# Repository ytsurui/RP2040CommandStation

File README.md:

# RP2040-Based DCC Command Station

underconstruction

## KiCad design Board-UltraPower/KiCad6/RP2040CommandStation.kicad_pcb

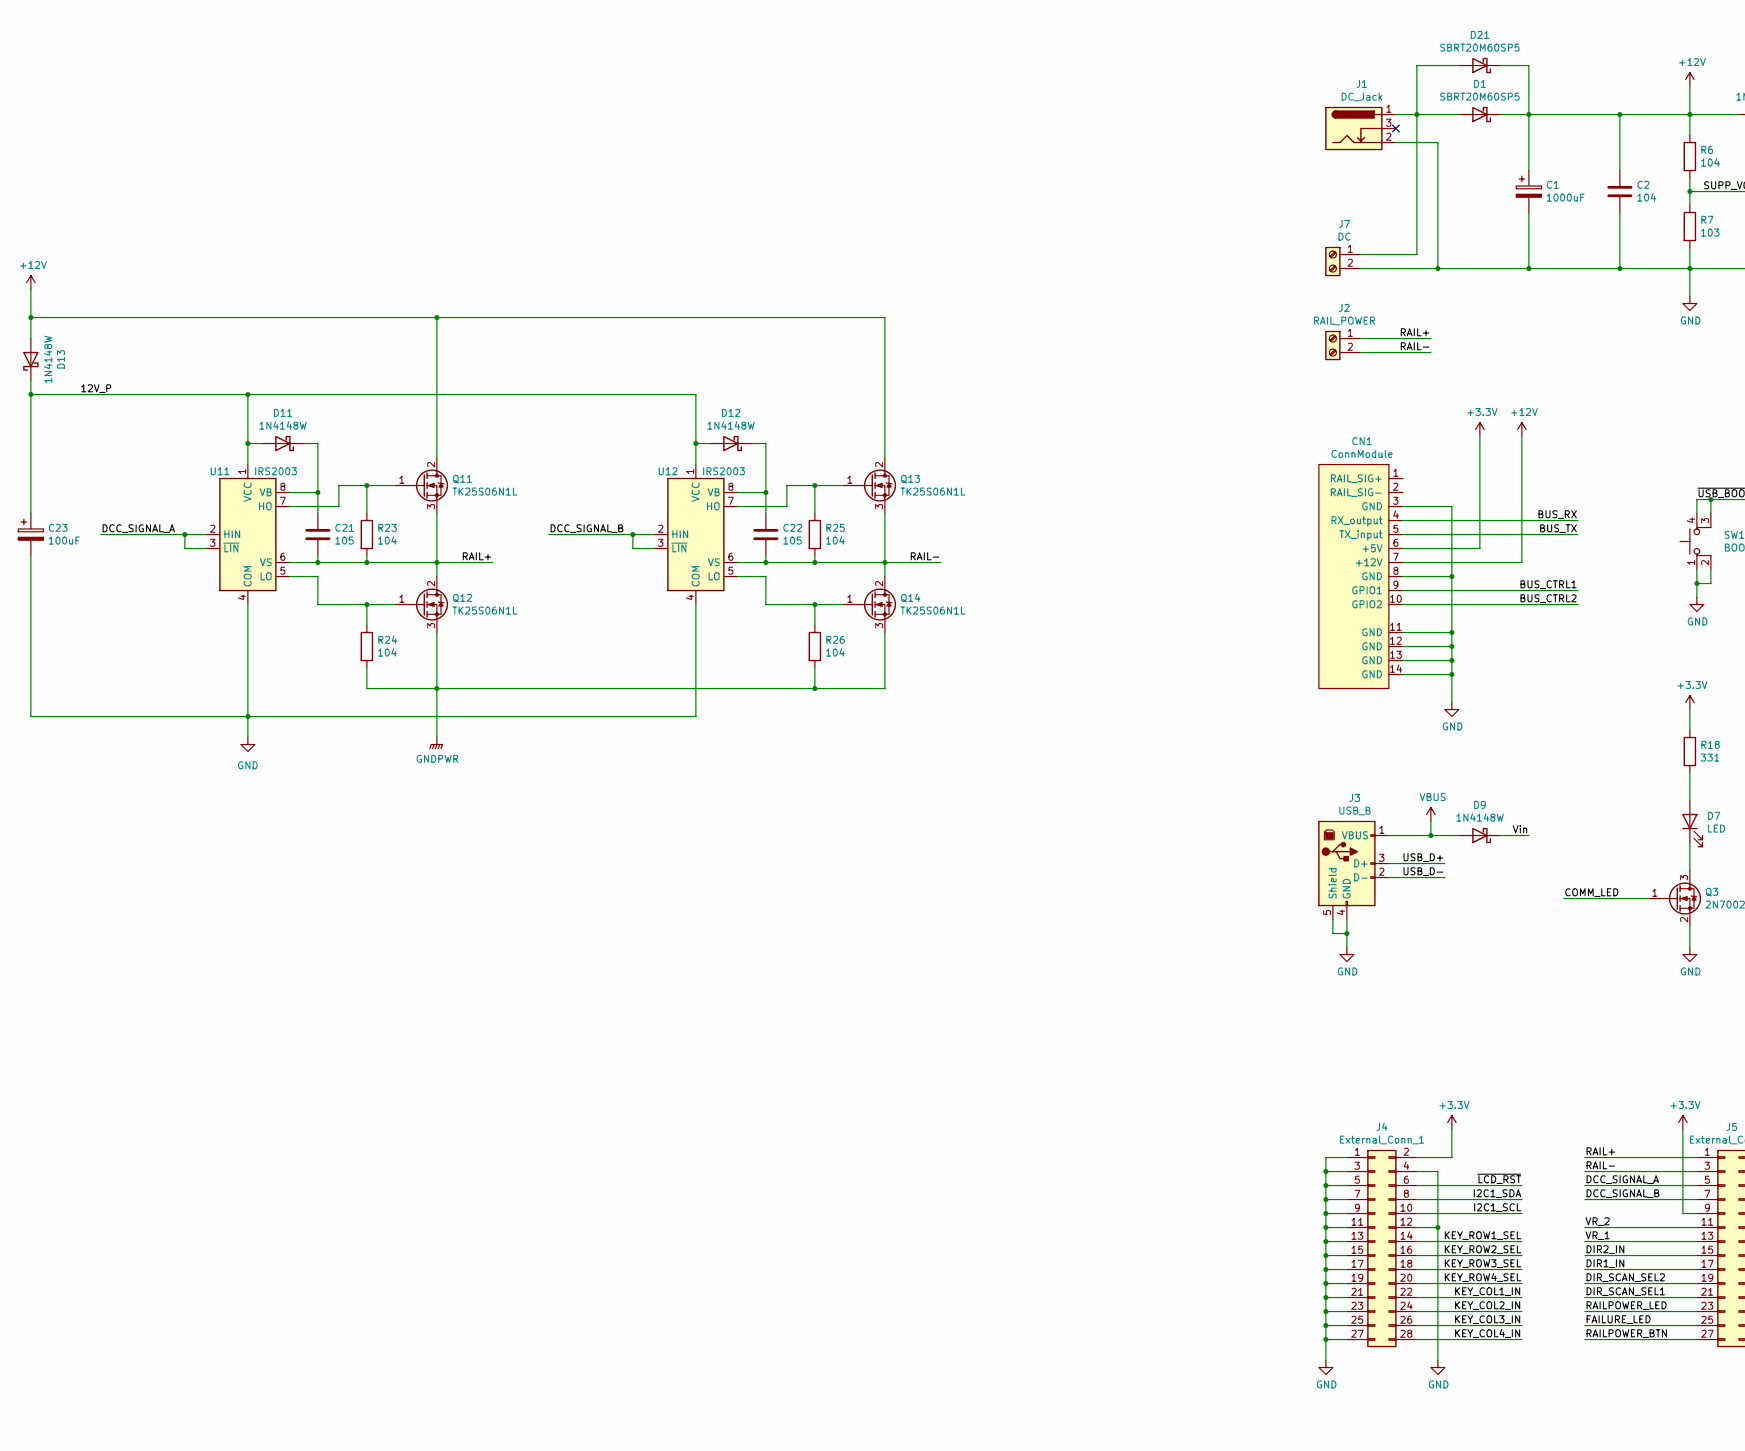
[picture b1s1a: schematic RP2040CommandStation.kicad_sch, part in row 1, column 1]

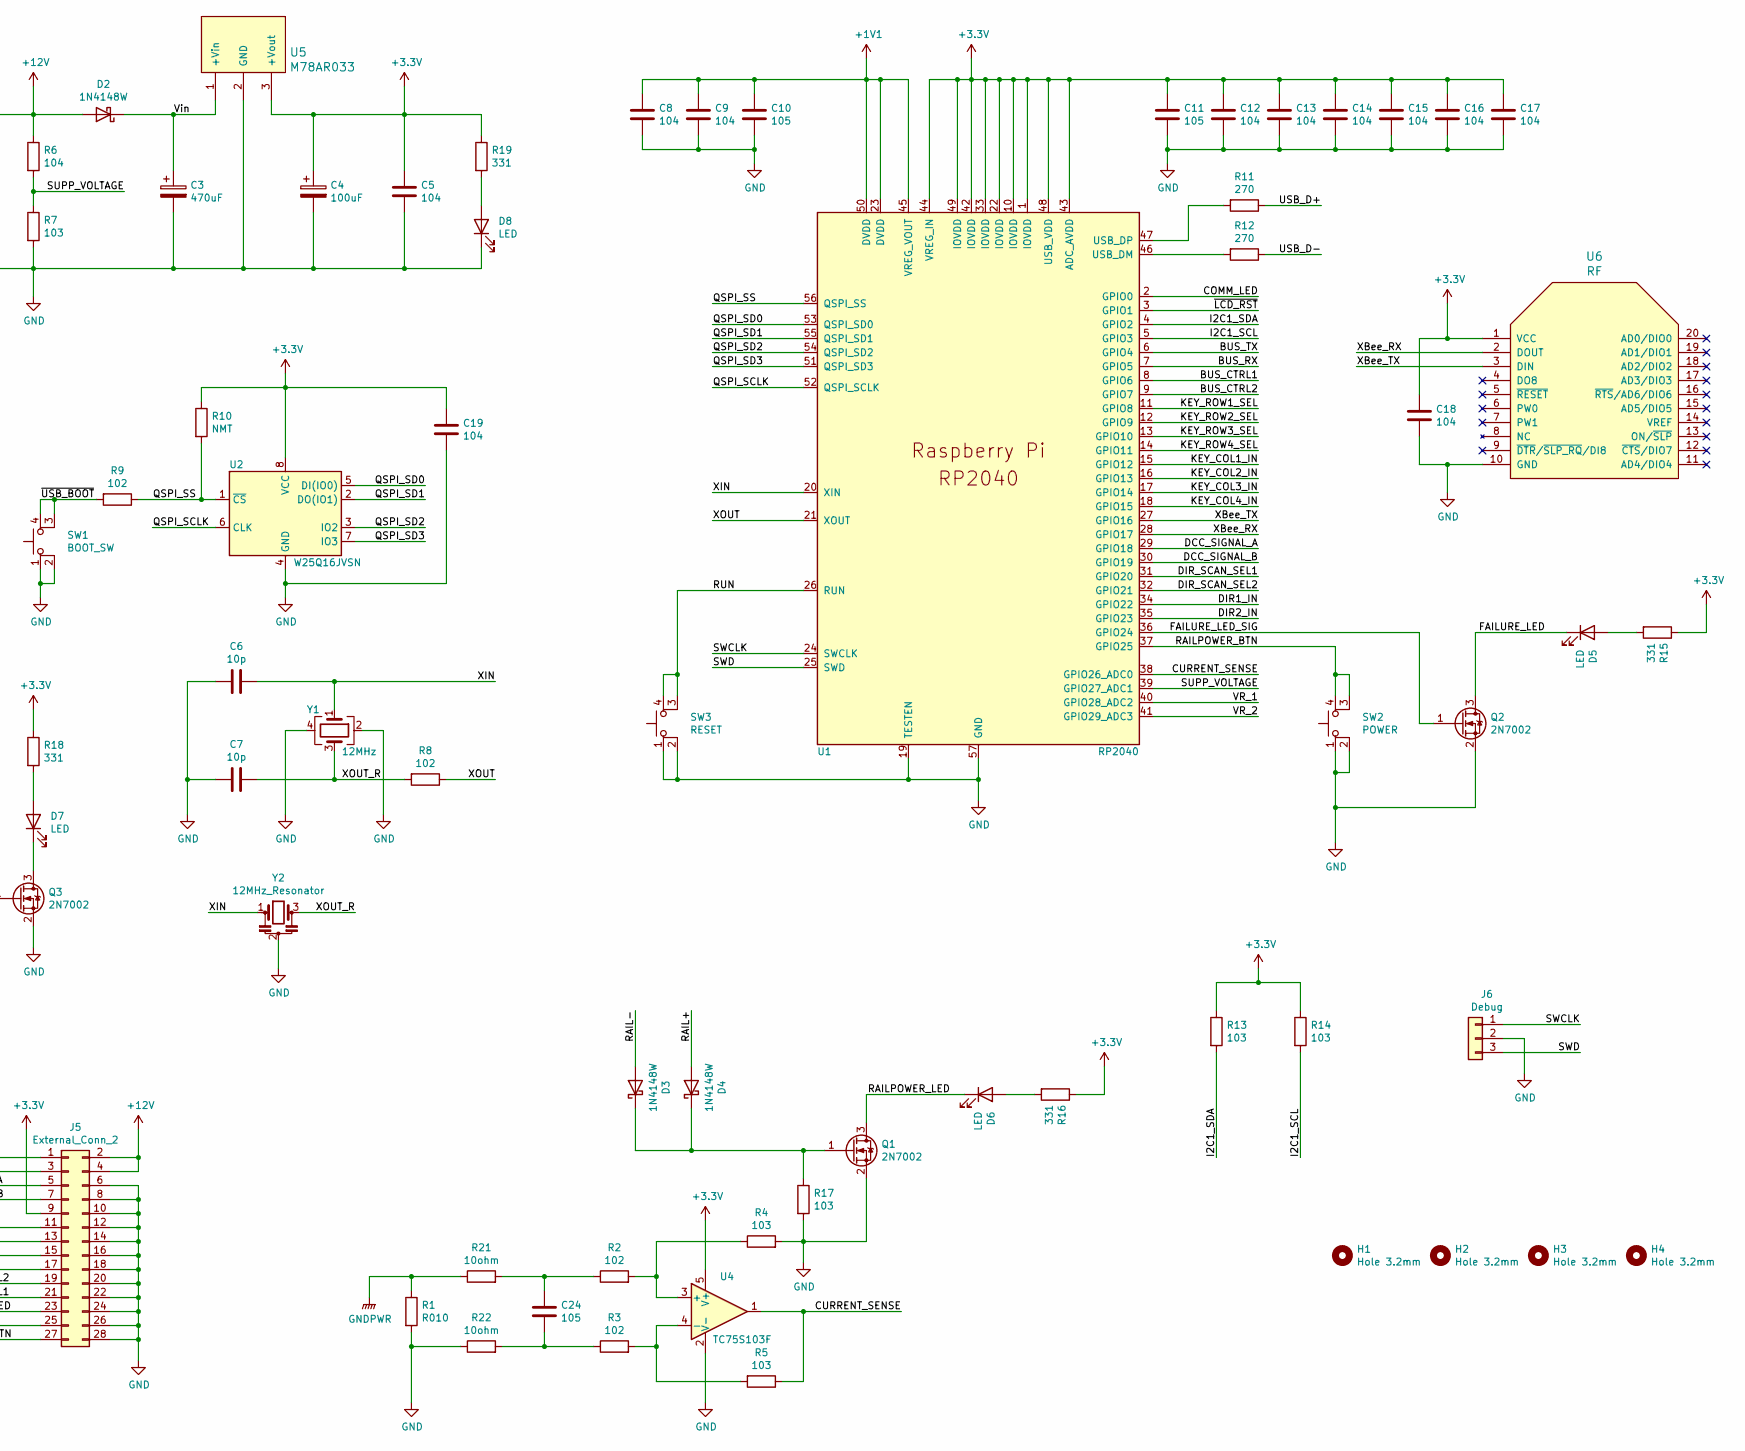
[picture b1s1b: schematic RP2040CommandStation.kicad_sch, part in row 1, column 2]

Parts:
C1: 1000uF; CAP_TH_12_5
C2, C5, C8, C9, C12, C13, C14, C15, C16, C17, C18, C19: 104; C_1005
C3: 470uF; CAP_TH_8x11_5
C4, C23: 100uF; CAP_TH_5x11
C6, C7: 10p; C_1005
C10, C11, C21, C22, C24: 105; C_1005
CN1: ConnModule; CommModuleTiny
D1, D21: SBRT20M60SP5; POWERDI5
D2, D3, D4, D9, D11, D12, D13: 1N4148W; SOD-123FL
D5, D6, D7, D8: LED; LED_3mm
H1, H2, H3, H4: Hole 3.2mm; HOLE_3.2mm
J1: DC_Jack; BARREL_JACK
J2: RAIL_POWER; TB111-2
J3: USB_B
J4: External_Conn_1; PinSocket_2x14_2_54mm
J5: External_Conn_2; PinSocket_2x14_2_54mm
J6: Debug; PinHeader_01x03
J7: DC; TB111-2
Q1, Q2, Q3: 2N7002; SOT-23
Q11, Q12, Q13, Q14: TK25S06N1L; DPAK+
R1: R010; R_6432
R2, R3, R8, R9: 102; R_1608
R4, R5, R7, R13, R14, R17: 103; R_1608
R6, R23, R24, R25, R26: 104; R_1608
R10: NMT; R_1608
R11, R12: 270; R_1608
R15, R16, R18, R19: 331; R_1608
R21, R22: 10ohm; R_1608
SW1: BOOT_SW; TS-0606
SW2: POWER; TS-0606
SW3: RESET; TS-0606
U1: RP2040; RP2040-QFN-56
U2: W25Q16JVSN; SO-8
U4: TC75S103F; SOT-23-5
U5: M78AR033; M78AR0XX
U6: RF; XBee
U11, U12: IRS2003; SO-8
Y1: 12MHz; FA-238_Crystal
Y2: 12MHz_Resonator; SMD_Resonator_3213

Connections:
+1V1: C8.1, C9.1, C10.1, U1.23 (DVDD), U1.45 (VREG_VOUT), U1.50 (DVDD)
+3.3V: C4.1, C5.1, C11.1, C12.1, C13.1, C14.1, C15.1, C16.1, C17.1, C18.1, C19.1, CN1.6 (+5V), J4.2, J5.9, R10.1, R13.1, R14.1, R15.1, R16.1, R18.1, R19.1, U1.1 (IOVDD), U1.10 (IOVDD), U1.22 (IOVDD), U1.33 (IOVDD), U1.42 (IOVDD), U1.43 (ADC_AVDD), U1.44 (VREG_IN), U1.48 (USB_VDD), U1.49 (IOVDD), U2.8 (VCC), U4.5 (V+), U5.3 (+Vout), U6.1 (VCC)
+12V: C1.1, C2.1, CN1.7 (+12V), D1.1 (K), D2.2 (A), D13.2 (A), D21.1 (K), J5.2, J5.4, Q11.2 (D), Q13.2 (D), R6.1
/12V_P: C23.1, D11.2 (A), D12.2 (A), D13.1 (K), U11.1 (VCC), U12.1 (VCC)
/BUS_CTRL1: CN1.9 (GPIO1), U1.8 (GPIO6)
/BUS_CTRL2: CN1.10 (GPIO2), U1.9 (GPIO7)
/BUS_RX: CN1.4 (RX_output), U1.7 (GPIO5)
/BUS_TX: CN1.5 (TX_input), U1.6 (GPIO4)
/COMM_LED: Q3.1 (G), U1.2 (GPIO0)
/CURRENT_SENSE: R5.1, U1.38 (GPIO26_ADC0), U4.1
/DCC_SIGNAL_A: J5.5, U1.29 (GPIO18), U11.2 (HIN), U11.3 (~LIN)
/DCC_SIGNAL_B: J5.7, U1.30 (GPIO19), U12.2 (HIN), U12.3 (~LIN)
/DIR1_IN: J5.17, U1.34 (GPIO22)
/DIR2_IN: J5.15, U1.35 (GPIO23)
/DIR_SCAN_SEL1: J5.21, U1.31 (GPIO20)
/DIR_SCAN_SEL2: J5.19, U1.32 (GPIO21)
/FAILURE_LED: D5.1 (K), J5.25, Q2.3 (D)
/FAILURE_LED_SIG: Q2.1 (G), U1.36 (GPIO24)
/I2C1_SCL: J4.10, R14.2, U1.5 (GPIO3)
/I2C1_SDA: J4.8, R13.2, U1.4 (GPIO2)
/KEY_COL1_IN: J4.22, U1.15 (GPIO12)
/KEY_COL2_IN: J4.24, U1.16 (GPIO13)
/KEY_COL3_IN: J4.26, U1.17 (GPIO14)
/KEY_COL4_IN: J4.28, U1.18 (GPIO15)
/KEY_ROW1_SEL: J4.14, U1.11 (GPIO8)
/KEY_ROW2_SEL: J4.16, U1.12 (GPIO9)
/KEY_ROW3_SEL: J4.18, U1.13 (GPIO10)
/KEY_ROW4_SEL: J4.20, U1.14 (GPIO11)
/QSPI_SCLK: U1.52 (QSPI_SCLK), U2.6 (CLK)
/QSPI_SD0: U1.53 (QSPI_SD0), U2.5 (DI(IO0))
/QSPI_SD1: U1.55 (QSPI_SD1), U2.2 (DO(IO1))
/QSPI_SD2: U1.54 (QSPI_SD2), U2.3 (IO2)
/QSPI_SD3: U1.51 (QSPI_SD3), U2.7 (IO3)
/QSPI_SS: R9.1, R10.2, U1.56 (QSPI_SS), U2.1 (~CS)
/RAIL+: C21.2, D4.2 (A), J2.1, J5.1, Q11.3 (S), Q12.2 (D), R23.2, U11.6 (VS)
/RAIL-: C22.2, D3.2 (A), J2.2, J5.3, Q13.3 (S), Q14.2 (D), R25.2, U12.6 (VS)
/RAILPOWER_BTN: J5.27, SW2.3 (K), SW2.4 (A), U1.37 (GPIO25)
/RAILPOWER_LED: D6.1 (K), J5.23, Q1.3 (D)
/RUN: SW3.3 (K), SW3.4 (A), U1.26 (RUN)
/SUPP_VOLTAGE: R6.2, R7.1, U1.39 (GPIO27_ADC1)
/SWCLK: J6.1, U1.24 (SWCLK)
/SWD: J6.3, U1.25 (SWD)
/USB_D+: J3.3 (D+), R11.1
/USB_D-: J3.2 (D-), R12.1
/VR_1: J5.13, U1.40 (GPIO28_ADC2)
/VR_2: J5.11, U1.41 (GPIO29_ADC3)
/Vin: C3.1, D2.1 (K), D9.1 (K), U5.1 (+Vin)
/XBee_RX: U1.28 (GPIO17), U6.2 (DOUT)
/XBee_TX: U1.27 (GPIO16), U6.3 (DIN)
/XIN: C6.1, U1.20 (XIN), Y1.1, Y2.1
/XOUT: R8.1, U1.21 (XOUT)
/XOUT_R: C7.1, R8.2, Y1.3, Y2.3
/~LCD_RST: J4.6, U1.3 (GPIO1)
/~USB_BOOT: R9.2, SW1.3 (K), SW1.4 (A)
GNDPWR: Q12.3 (S), Q14.3 (S), R1.1, R21.1, R24.2, R26.2
unnamed: C21.1, D11.1 (K), U11.8 (VB)
unnamed: C22.1, D12.1 (K), U12.8 (VB)
unnamed: C24.1, R2.1, R21.2
unnamed: C24.2, R3.1, R22.2
unnamed: D1.2 (A), D21.2 (A), J1.1, J7.1
unnamed: D3.1 (K), D4.1 (K), Q1.1 (G), R17.1
unnamed: D5.2 (A), R15.2
unnamed: D6.2 (A), R16.2
unnamed: D7.1 (K), Q3.3 (D)
unnamed: D7.2 (A), R18.2
unnamed: D8.2 (A), R19.2
unnamed: Q11.1 (G), R23.1, U11.7 (HO)
unnamed: Q13.1 (G), R25.1, U12.7 (HO)
unnamed: Q14.1 (G), R26.1, U12.5 (LO)
unnamed: R2.2, R4.1, U4.3 (+)
unnamed: R3.2, R5.2, U4.4 (-)
unnamed: R11.2, U1.47 (USB_DP)
unnamed: R12.2, U1.46 (USB_DM)
unnamed: Q12.1 (G), R24.1, U11.5 (LO)
VBUS: D9.2 (A), J3.1 (VBUS)

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
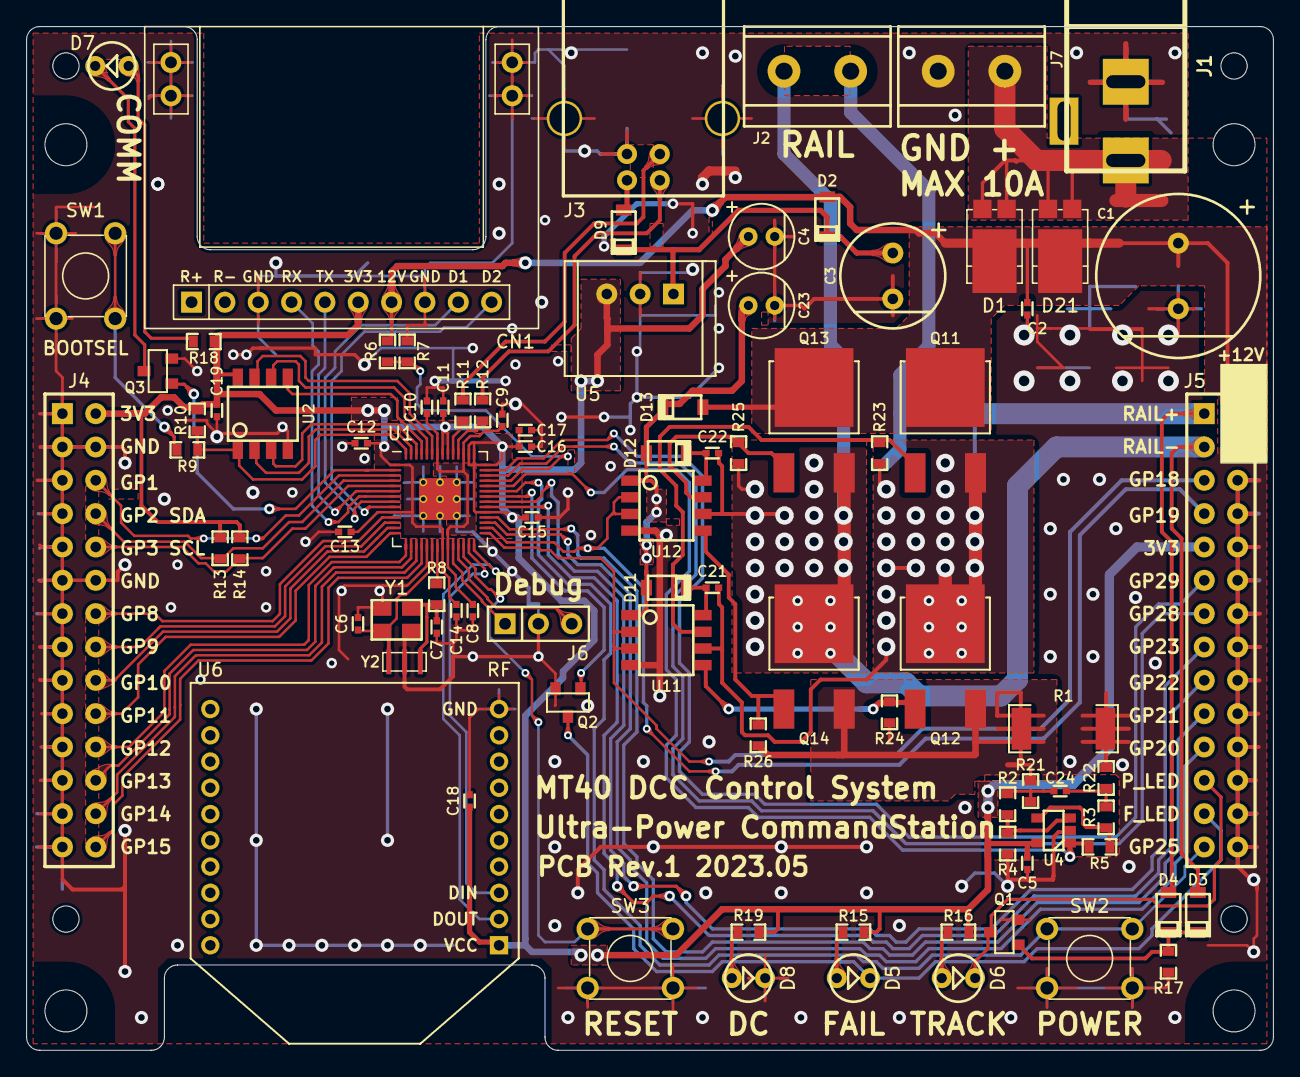
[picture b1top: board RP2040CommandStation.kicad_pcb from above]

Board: 2 copper layers, 95.0 x 78.0 mm, 92 parts (0 on the bottom side), 76 nets.

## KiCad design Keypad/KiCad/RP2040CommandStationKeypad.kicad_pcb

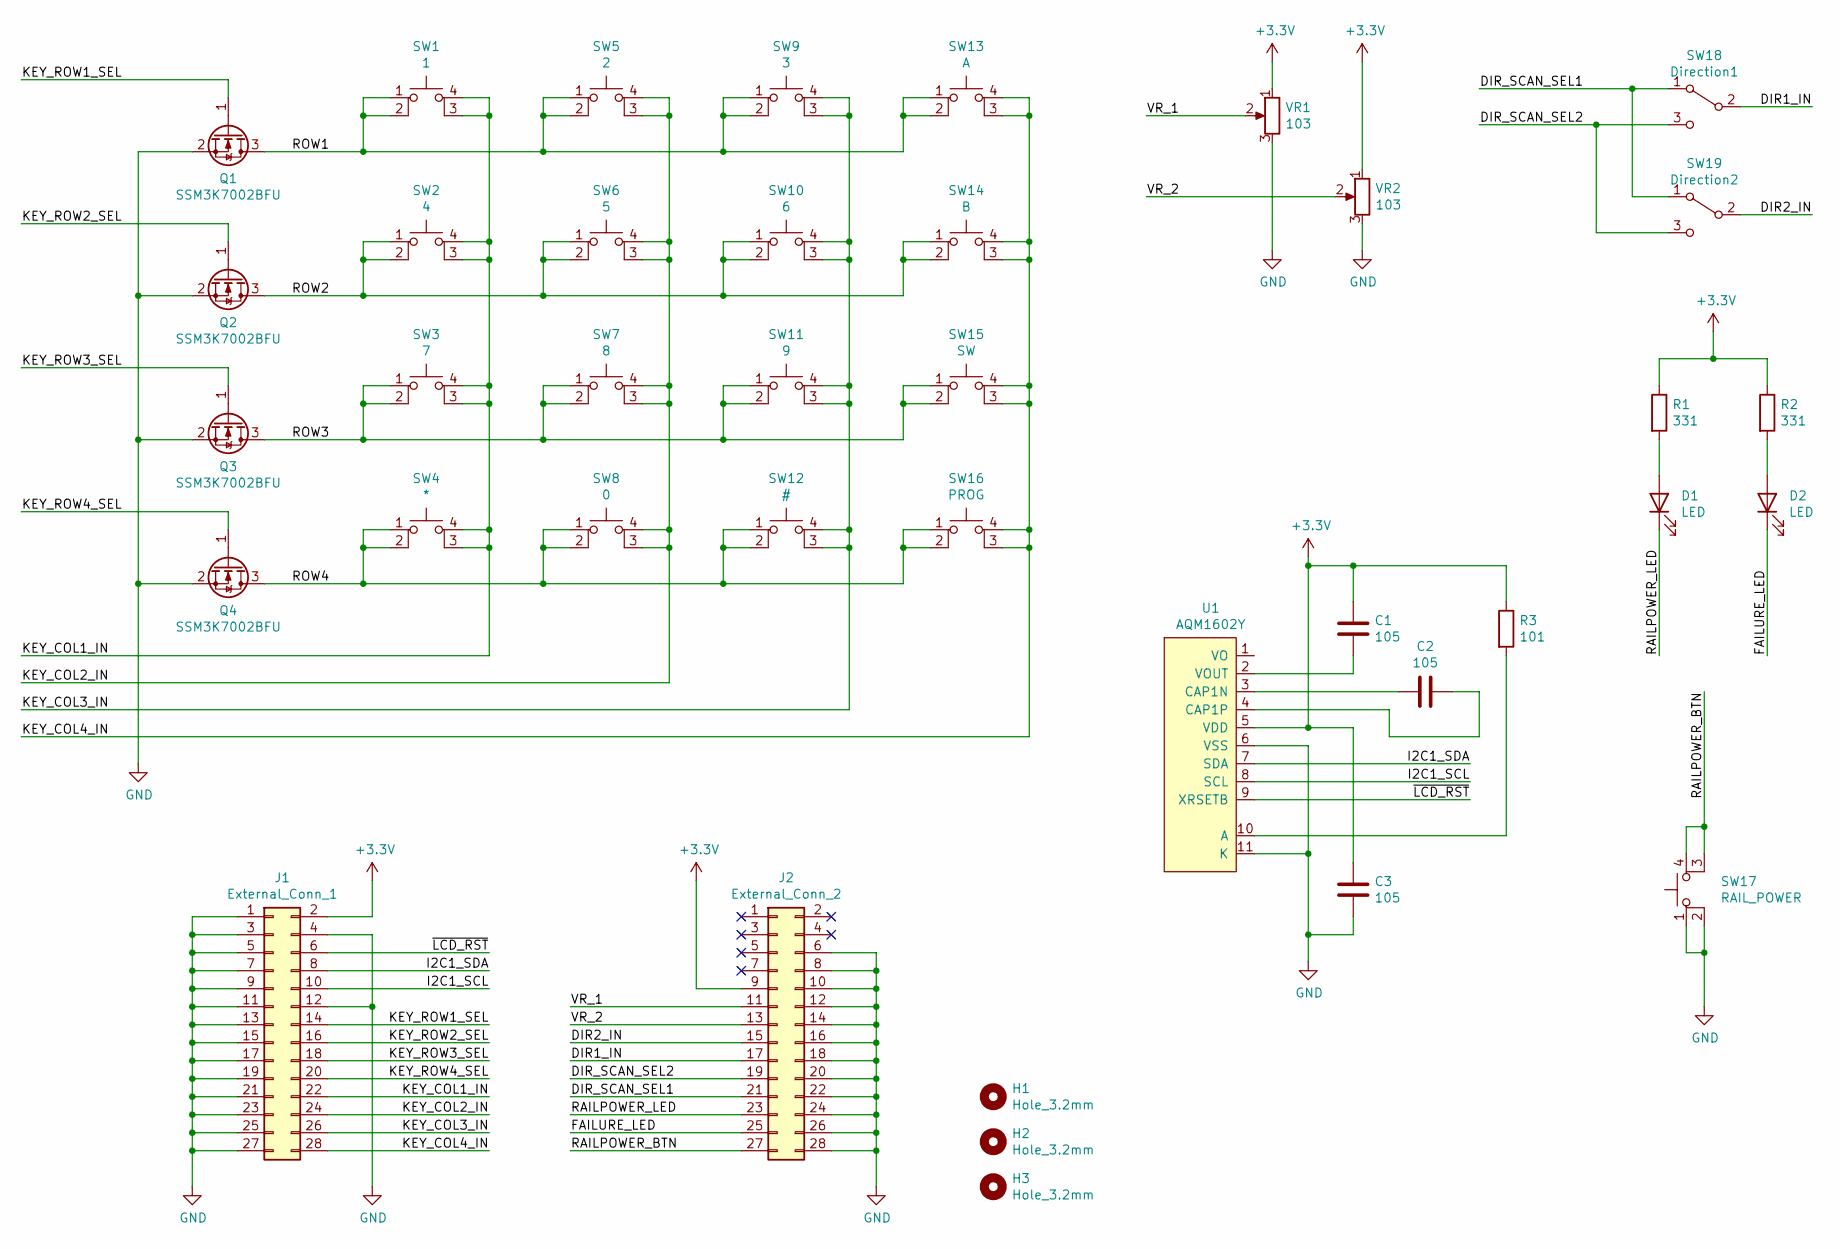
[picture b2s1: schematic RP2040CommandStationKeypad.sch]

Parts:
C1, C2, C3: 105; C_1005
D1, D2: LED; LED_3mm
H1, H2, H3: Hole_3.2mm; HOLE_3.2mm
J1: External_Conn_1; PinHeader_Reverse_2x14_2_54mm
J2: External_Conn_2; PinHeader_Reverse_2x14_2_54mm
Q1, Q2, Q3, Q4: SSM3K7002BFU; SC-70
R1, R2: 331; R_1608
R3: 101; R_1608
SW1: 1; TS-0606
SW2: 4; TS-0606
SW3: 7; TS-0606
SW4: *; TS-0606
SW5: 2; TS-0606
SW6: 5; TS-0606
SW7: 8; TS-0606
SW8: 0; TS-0606
SW9: 3; TS-0606
SW10: 6; TS-0606
SW11: 9; TS-0606
SW12: #; TS-0606
SW13: A; TS-0606
SW14: B; TS-0606
SW15: SW; TS-0606
SW16: PROG; TS-0606
SW17: RAIL_POWER; TS-0606
SW18: Direction1; TOGGLE_SW_1C
SW19: Direction2; TOGGLE_SW_1C
U1: AQM1602Y
VR1, VR2: 103; ALPS-SLIDEVOLUME

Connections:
+3V3: C1.1, C3.1, J1.2, J2.9, R1.1, R2.1, R3.1, U1.5 (VDD), VR1.1, VR2.1
/DIR1_IN: J2.17, SW18.2 (B)
/DIR2_IN: J2.15, SW19.2 (B)
/DIR_SCAN_SEL1: J2.21, SW18.1 (A), SW19.1 (A)
/DIR_SCAN_SEL2: J2.19, SW18.3 (C), SW19.3 (C)
/FAILURE_LED: D2.1 (K), J2.25
/I2C1_SCL: J1.10, U1.8 (SCL)
/I2C1_SDA: J1.8, U1.7 (SDA)
/KEY_COL1_IN: J1.22, SW1.3 (K), SW1.4 (A), SW2.3 (K), SW2.4 (A), SW3.3 (K), SW3.4 (A), SW4.3 (K), SW4.4 (A)
/KEY_COL2_IN: J1.24, SW5.3 (K), SW5.4 (A), SW6.3 (K), SW6.4 (A), SW7.3 (K), SW7.4 (A), SW8.3 (K), SW8.4 (A)
/KEY_COL3_IN: J1.26, SW9.3 (K), SW9.4 (A), SW10.3 (K), SW10.4 (A), SW11.3 (K), SW11.4 (A), SW12.3 (K), SW12.4 (A)
/KEY_COL4_IN: J1.28, SW13.3 (K), SW13.4 (A), SW14.3 (K), SW14.4 (A), SW15.3 (K), SW15.4 (A), SW16.3 (K), SW16.4 (A)
/KEY_ROW1_SEL: J1.14, Q1.1 (G)
/KEY_ROW2_SEL: J1.16, Q2.1 (G)
/KEY_ROW3_SEL: J1.18, Q3.1 (G)
/KEY_ROW4_SEL: J1.20, Q4.1 (G)
/RAILPOWER_BTN: J2.27, SW17.3 (K), SW17.4 (A)
/RAILPOWER_LED: D1.1 (K), J2.23
/ROW1: Q1.3 (D), SW1.1, SW1.2, SW5.1, SW5.2, SW9.1, SW9.2, SW13.1, SW13.2
/ROW2: Q2.3 (D), SW2.1, SW2.2, SW6.1, SW6.2, SW10.1, SW10.2, SW14.1, SW14.2
/ROW3: Q3.3 (D), SW3.1, SW3.2, SW7.1, SW7.2, SW11.1, SW11.2, SW15.1, SW15.2
/ROW4: Q4.3 (D), SW4.1, SW4.2, SW8.1, SW8.2, SW12.1, SW12.2, SW16.1, SW16.2
/VR_1: J2.11, VR1.2
/VR_2: J2.13, VR2.2
/~LCD_RST: J1.6, U1.9 (XRSETB)
GND: C3.2, J1.1, J1.3, J1.4, J1.5, J1.7, J1.9, J1.11, J1.12, J1.13, J1.15, J1.17, J1.19, J1.21, J1.23, J1.25, J1.27, J2.6, J2.8, J2.10, J2.12, J2.14, J2.16, J2.18, J2.20, J2.22, J2.24, J2.26, J2.28, Q1.2 (S), Q2.2 (S), Q3.2 (S), Q4.2 (S), SW17.1, SW17.2, U1.6 (VSS), U1.11 (K), VR1.3, VR2.3
unnamed: C1.2, U1.2 (VOUT)
unnamed: C2.1, U1.4 (CAP1P)
unnamed: C2.2, U1.3 (CAP1N)
unnamed: D1.2 (A), R1.2
unnamed: D2.2 (A), R2.2
unnamed: R3.2, U1.10 (A)

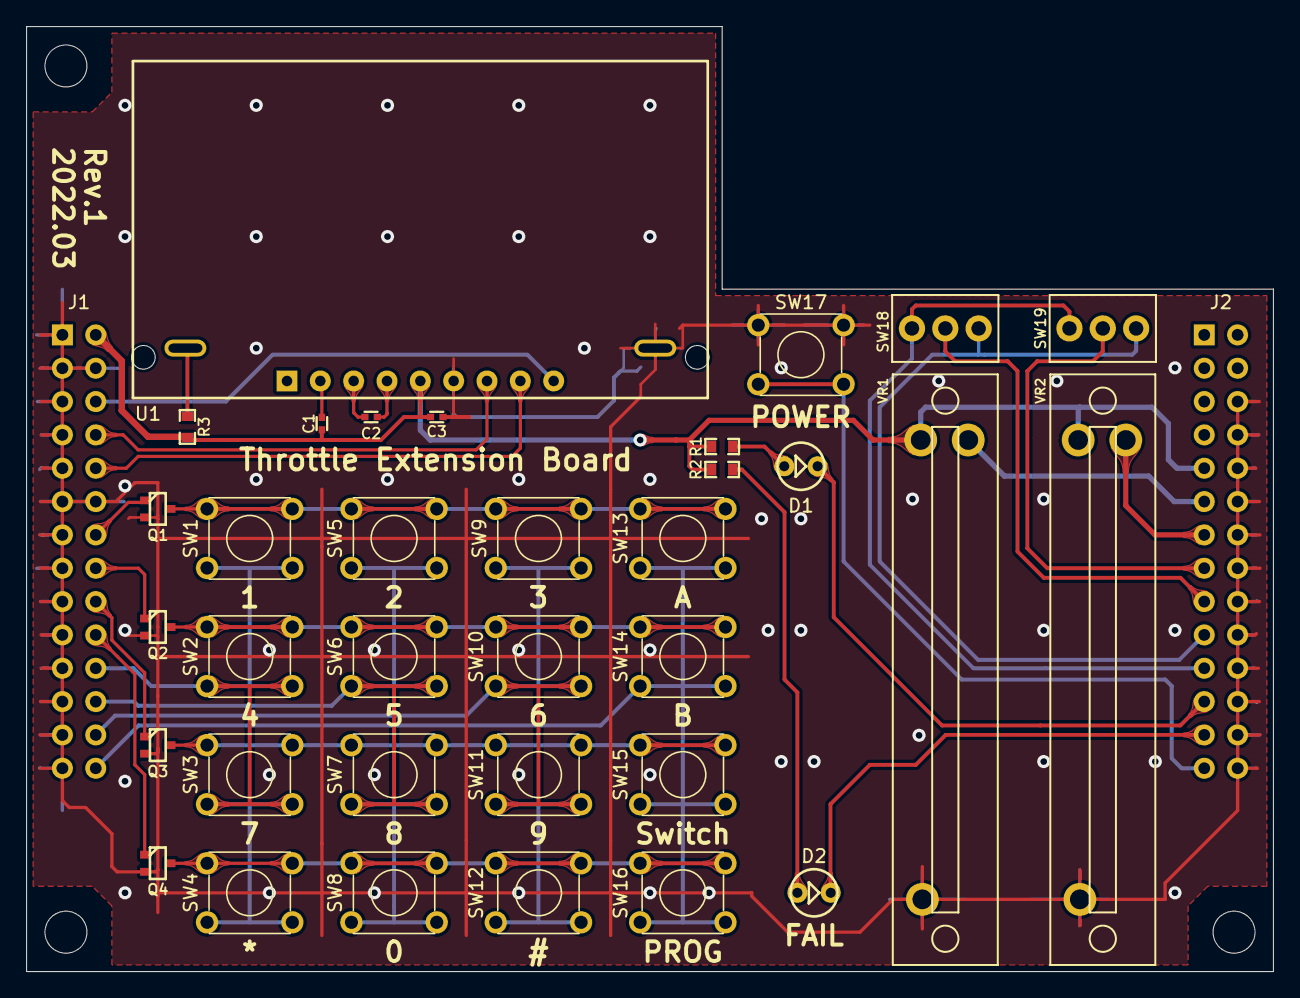
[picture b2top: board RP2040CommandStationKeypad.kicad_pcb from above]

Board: 2 copper layers, 95.0 x 72.0 mm, 39 parts (0 on the bottom side), 32 nets.

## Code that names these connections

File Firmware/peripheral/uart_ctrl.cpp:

#include "pico/stdlib.h"
#include "uart_ctrl.h"

#define BUS_TX_GPIO 4
#define BUS_RX_GPIO 5
#define BUS_CTRL1_GPIO 6
#define BUS_CTRL2_GPIO 7
#define WIRELESS_TX_GPIO 16
#define WIRELESS_RX_GPIO 17

#define DEFAULT_BAUDRATE 115200

bool uartCtrl::bridgeModeStat;
uartCtrl uartCtrl::uartCtrlInst[2];

void uartCtrl::globalInit(void)
{
    // Wireless Port Pre-Init (for XBee3)
    gpio_init(WIRELESS_TX_GPIO);
    gpio_init(WIRELESS_RX_GPIO);
    gpio_pull_up(WIRELESS_TX_GPIO);
    gpio_pull_up(WIRELESS_RX_GPIO);
    gpio_set_dir(WIRELESS_TX_GPIO, false);
    gpio_set_dir(WIRELESS_RX_GPIO, false);

    gpio_init(BUS_TX_GPIO);
    gpio_init(BUS_RX_GPIO);
    gpio_pull_up(BUS_TX_GPIO);
    gpio_pull_up(BUS_RX_GPIO);
    gpio_set_dir(BUS_TX_GPIO, false);
    gpio_set_dir(BUS_RX_GPIO, false);

    uartCtrlInst[0].uartModule = uart1;
    uartCtrlInst[1].uartModule = uart0;

    uartCtrlInst[0].gpio_rx_num = BUS_RX_GPIO;
    uartCtrlInst[0].gpio_tx_num = BUS_TX_GPIO;
    uartCtrlInst[1].gpio_rx_num = WIRELESS_RX_GPIO;
    uartCtrlInst[1].gpio_tx_num = WIRELESS_TX_GPIO;

    uartCtrlInst[0].init();
    uartCtrlInst[1].init();
}

void uartCtrl::globalTask(void)
{
    uartCtrlInst[0].task();
    uartCtrlInst[1].task();
}

uartCtrl *uartCtrl::getInstance(uint8_t id)
{
    if (id >= 2)
    {
        return nullptr;
    }
    return &uartCtrlInst[id];
}

void uartCtrl::init(void)
{
    if (baudRate == 0)
    {
        baudRate = DEFAULT_BAUDRATE;
    }
    recvCb = nullptr;
    gpio_init(gpio_tx_num);
    gpio_init(gpio_rx_num);
    uart_init(uartModule, baudRate);
    gpio_set_function(gpio_tx_num, GPIO_FUNC_UART);
    gpio_set_function(gpio_rx_num, GPIO_FUNC_UART);
    uart_is_enabled(uartModule);
}

void uartCtrl::task(void)
{
    uint8_t recv;

    while (uart_is_readable(uartModule))
    {
        recv = uart_getc(uartModule);
        if (recvCb != nullptr)
        {
            recvCb(recv);
        }
    }
}

void uartCtrl::send(uint8_t data)
{
    while (!uart_is_writable(uartModule))
        ;
    uart_putc(uartModule, data);
}

void uartCtrl::setBaudRate(int baud)
{
    baudRate = baud;
    uart_init(uartModule, baudRate);
    uart_is_enabled(uartModule);
}

void uartCtrl::setRecvCallback(void (*cb)(uint8_t))
{
    recvCb = cb;
}

void uartCtrl::evacuationCallback()
{
    evacuationCb = recvCb;
    recvCb = nullptr;
}

void uartCtrl::restoreCallback()
{
    recvCb = evacuationCb;
    evacuationCb = nullptr;
}

void uartCtrl::clearRecvCallback()
{
    recvCb = nullptr;
}   

void uartCtrl::BusGPIOdir(uint8_t num, bool dir, bool pullup)
{
    uint8_t gpioNum;
    if (num == 0) {
        gpioNum = BUS_CTRL1_GPIO;
    } else if (num == 1) {
        gpioNum = BUS_CTRL2_GPIO;
    } else {
        return;
    }

    gpio_set_dir(gpioNum, dir);
    if (!dir && pullup) {
        gpio_pull_up(gpioNum);
    } 
}

void uartCtrl::putBusGPIO(uint8_t num, bool value)
{
    uint8_t gpioNum;
    if (num == 0) {
        gpioNum = BUS_CTRL1_GPIO;
    } else if (num == 1) {
        gpioNum = BUS_CTRL2_GPIO;
    } else {
        return;
    }

    gpio_put(gpioNum, value);
}

bool uartCtrl::getBusGPIO(uint8_t num)
{
    uint8_t gpioNum;
    if (num == 0) {
        gpioNum = BUS_CTRL1_GPIO;
    } else if (num == 1) {
        gpioNum = BUS_CTRL2_GPIO;
    } else {
        return false;
    }

    return gpio_get(gpioNum);
}

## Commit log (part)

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2023-05-19 ボタン類の動作を調整
2023-05-19 Loconetの車両アドレス解放後の動作を修正
2023-05-19 大出力版の設定を追加
2023-05-19 デバッグ用メッセージを追加
2023-05-23 列車オブジェクトを取得時に見つからない場合は自動生成する機能を追加
2023-05-23 Loconetのタイムアウト間隔を調整
2023-05-23 独自通信バスの関数群荒削り版の追加
2023-05-23 ビルド時に独自バスのソースコードを読み込むように変更
2023-05-23 環境変数のPICO_SDK_PATHを強制的に読み込むように変更
2023-05-24 線路電源状態の取得用関数を追加
2023-05-24 初期動作テスト用の調整・デバッグ用機能の追加
2023-05-24 通信バスプロトコルを独自のものに変更
2023-05-24 データ送出用関数を追加
2023-05-24 コマンド文字列中のスペースを無視するように変更
2023-05-24 独自バス: ステータス取得(電源/アクセサリ)を追加
2023-05-25 列車速度の読み出し機能を追加
2023-05-25 データ読み出しパケットの処理系を追加
2023-05-25 スペース処理のバグを修正
2023-05-27 通信バス用GPIOの処理を追加
2023-05-27 Carrier-Senseの処理を仮追加
2023-05-29 ECHO / CPS / LBUSコマンドの処理を追加
2023-05-30 電流設定方法をCMakeLists.txtに移動 / CPSコマンドに最大電流が出力されるように変更
2023-05-30 複数チャネルからのデータ受信に対応するように変更
2023-05-30 USBコマンド受信機能の追加 / コマンド終了文字の変更 / ゼロデータ命令の取り扱い不具合を修正
2023-05-30 デバッグメッセージの出力を抑制
2023-05-30 電流値の設定方法を変更
2023-06-03 アクセサリ出力の極性反転を修正
2023-06-03 LBUSの送信処理を全て処理するコールバック機能を追加
2023-06-03 MT40BUSにオフロードされたLBUSプロトコルの処理機能を追加
2023-06-03 defineでLBUSの処理を切り替えられるように変更
2023-06-03 UltraPower版の基板設計データを追加
2023-06-09 ローカルパケットの識別に対応
2023-06-09 認識可能な10進数の桁数を増加
2023-06-10 4文字コマンドが処理できない問題を修正
2023-06-14 L-BUSのパケット処理不具合を修正
2023-06-14 F29-F68の制御処理・パケット処理を追加
2023-06-14 TOSコマンドで出力されるステータスが反転していた問題を修正
2023-06-30 Loconetの受信処理を修正 / 受信時USBへのルーティングを削除
2023-06-30 不明なパケットの対応を追加
2023-06-30 パケット送信時の遅延を修正
2023-06-30 F29-F68の対応漏れを修正
2023-06-30 起動時のバージョン情報表示機能を追加
2023-07-17 無線側にMT40BUSの応答を返さない不具合を修正
2023-07-17 private packetの処理を追加
2023-08-06 Root/Robotモードの実装準備
2023-09-19 Root/Robotモード時の制御で、 lastCtrlCounterをリセットするように変更
2023-09-19 電源ボタンの挙動を改善
2023-09-19 キーパッドのチャタリング改善
2023-12-14 プログラム線路の挙動を修正
2023-12-17 PowerManagerの制御コマンドを追加
2023-12-17 L-BUSの電源オンオフコマンドをPowerManagerに連携
2024-01-12 PW / PWTコマンド実行後にPWSコマンドによる状態出力を実施する機能を追加
2024-01-12 Cutout Statusのコマンド実行定義を追加
2024-01-12 本体の電源ボタン操作を行った際にPWSコマンドを送出する機構を追加
2024-01-12 未知のコマンドを受信した際にフリーズする問題の修正
2024-01-12 アドレス指定なしのPMUPコマンド送出時に不要コマンドが送信される問題の修正
2024-01-12 本体のPOWERボタンを押した際に、PMUPコマンドを送出する機能を追加
2024-01-15 コマンド解析エンジンの変更テスト
2024-01-17 パケット受信処理を環境依存しない構造に変更
2024-01-17 PMUPパケットの送信に遅延を持たせるように変更
2024-03-13 '0'のパルス間隔を変更 (デコーダ誤動作対策)
2024-03-14 BiDi Cutoutのオンオフ切り替えを追加
2024-03-14 BiDi Commandの追加
2024-03-15 パケットデータ破棄の条件を変更
2024-03-15 データ送信開始時に前コマンドを完了させるように変更
2024-03-15 速度情報が規定値から溢れた時の処理を変更
2024-03-15 バージョン番号を変更
2024-06-22 robotctrl: if文のバグを修正
2024-06-22 Root/Robotモード: RDIT commandのバグを修正
2024-06-22 Root/Robotモード: 操作時に即座に速度・進行方向が反映されるように変更
2024-06-22 電圧モニタ: 緊急停止作動の電源電圧レベルを緩和
2024-08-16 overcurrent shutdownのデバッグメッセージを削除
2025-03-08 Root/Robotモード: 不正値対策と受信時の内部カウンタ処理を追加
2025-03-08 無線モジュールの初期化機能を追加
2025-03-08 データ送信: 32ビットの限界値近くに対応していない問題の修正 / private packetに対応
2025-03-08 WCFGコマンド (無線モジュール設定取得) に対応
2025-03-08 WCFGコマンド関連のファイルをCMakeListに追加
2025-09-09 F13以降のパケット送出タイミングの計算バグを修正
2025-12-24 列車制御の初期化バグ、14/28スピードステップのバグを修正
2025-12-24 パケットスケジューラの調整
